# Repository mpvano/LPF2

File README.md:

## The LPF2 Filter Board

LPF2 is a combined Relay Switched Harmonic Filter, Receiver High Pass Filter, VSWR bridge and Antenna Relay board for Low Powered HF Radios. It is designed primarily for use with radio board sets that stack mechanically with the Raspberry Pi. and has been successfully used to build several different radios.

The LPF2 board is compatible for stacking with boards designed to the Raspberry Pi "Hat" specification, although it is not a "hat" as it is the same size as the Pi itself and overhangs the IO connectors. It can also be used as a standalone board with anything that can provide compatible I2C and TX/RX control signals, and 3.3 Volt and Relay Power.

It can be built to use 4.5 Volt relays powered from the GPIO connector or for 12 Volt relays powered from an external source.

## N2ADR Filter Compatibility

The board was designed for limited software compatibility with the popular N2ADR filter board used by the Hermes Lite 2 radio and widely supported in SDR software. The board is NOT completely compatible with N2ADR's design. It differs in the following ways:

  1. The receiver low pass filter is always active - the control bit is IGNORED
  2. There are only 5 Low Pass filters. The control bit for "160 meters" is IGNORED.
  3. The Most significant bit of the control word is wire or'ed with the external Transmit/Receive line allowing software T/R switching.
  4. The VSWR bridge uses a different ADC, so that it does not conflict with any HL2 compatible hardware in the radio - but this means it is not directly displayable by SDR software expecting the HL2 VSWR ADC.

The board has been used primarily with "Radioberry" and "RadioHat" Boards to build 5-10 watt 3-30Mhz Multimode Ham Transceivers.

## Filter Component Selection

The Low Pass Filters are not suitable for extremely dirty power amplifiers. They are designed to reduce the harmonic emissions from properly designed amplifiers within legal limits by reducing the harmonics - not totally eliminating them. As such, they may not work with single ended power amplifiers without modification to the filter values - The design expects the 2nd harmonic to be somewhat reduced by the power amplifier.

The filter component values are based on the popular ones originally published by the RSGB.

The VSWR bridge transformers are conservatively designed so that the diodes are protected in the event of higher power being applied. To improve the sensitivity, reduce the ratio to 10:1 or 7:1 and adjust the software used for power calculation accordingly.

Variations in filter material batches may requre trimming the Toroid coil values by 1 or two turns or spreading or compacting them.

## Hints

I suggest testing the board's logic functionality while assembling it before the relays and filter components are installed since rework is difficult once the relays are in place.

I've also provided the source for a simple TK python program I use to view the VSWR, power and battery voltage in a separate window on my radios.

## Disclaimers

I designed this board for my own use. I have no plans to provide PCBs or boards to others at this time. Hopefully, if there is interest in this board others will provide for group builds, completed boards, or group purchases.

Anyone may use this design for any purpose whatsoever, although I would prefer that it retain some credit to me as the original designer. I will not provide support for any boards using this design that have not been actually built by ME!

If you build any boards or devices using this design, you are totally responsible for any associated liabilities.

This design was only possible thanks to the excellent work done by George Dobbs G3RJV, James Ahlstrom N2ADR, and everyone associated with the HL2 and Radioberry projects.

Mario Vano
AE0GL

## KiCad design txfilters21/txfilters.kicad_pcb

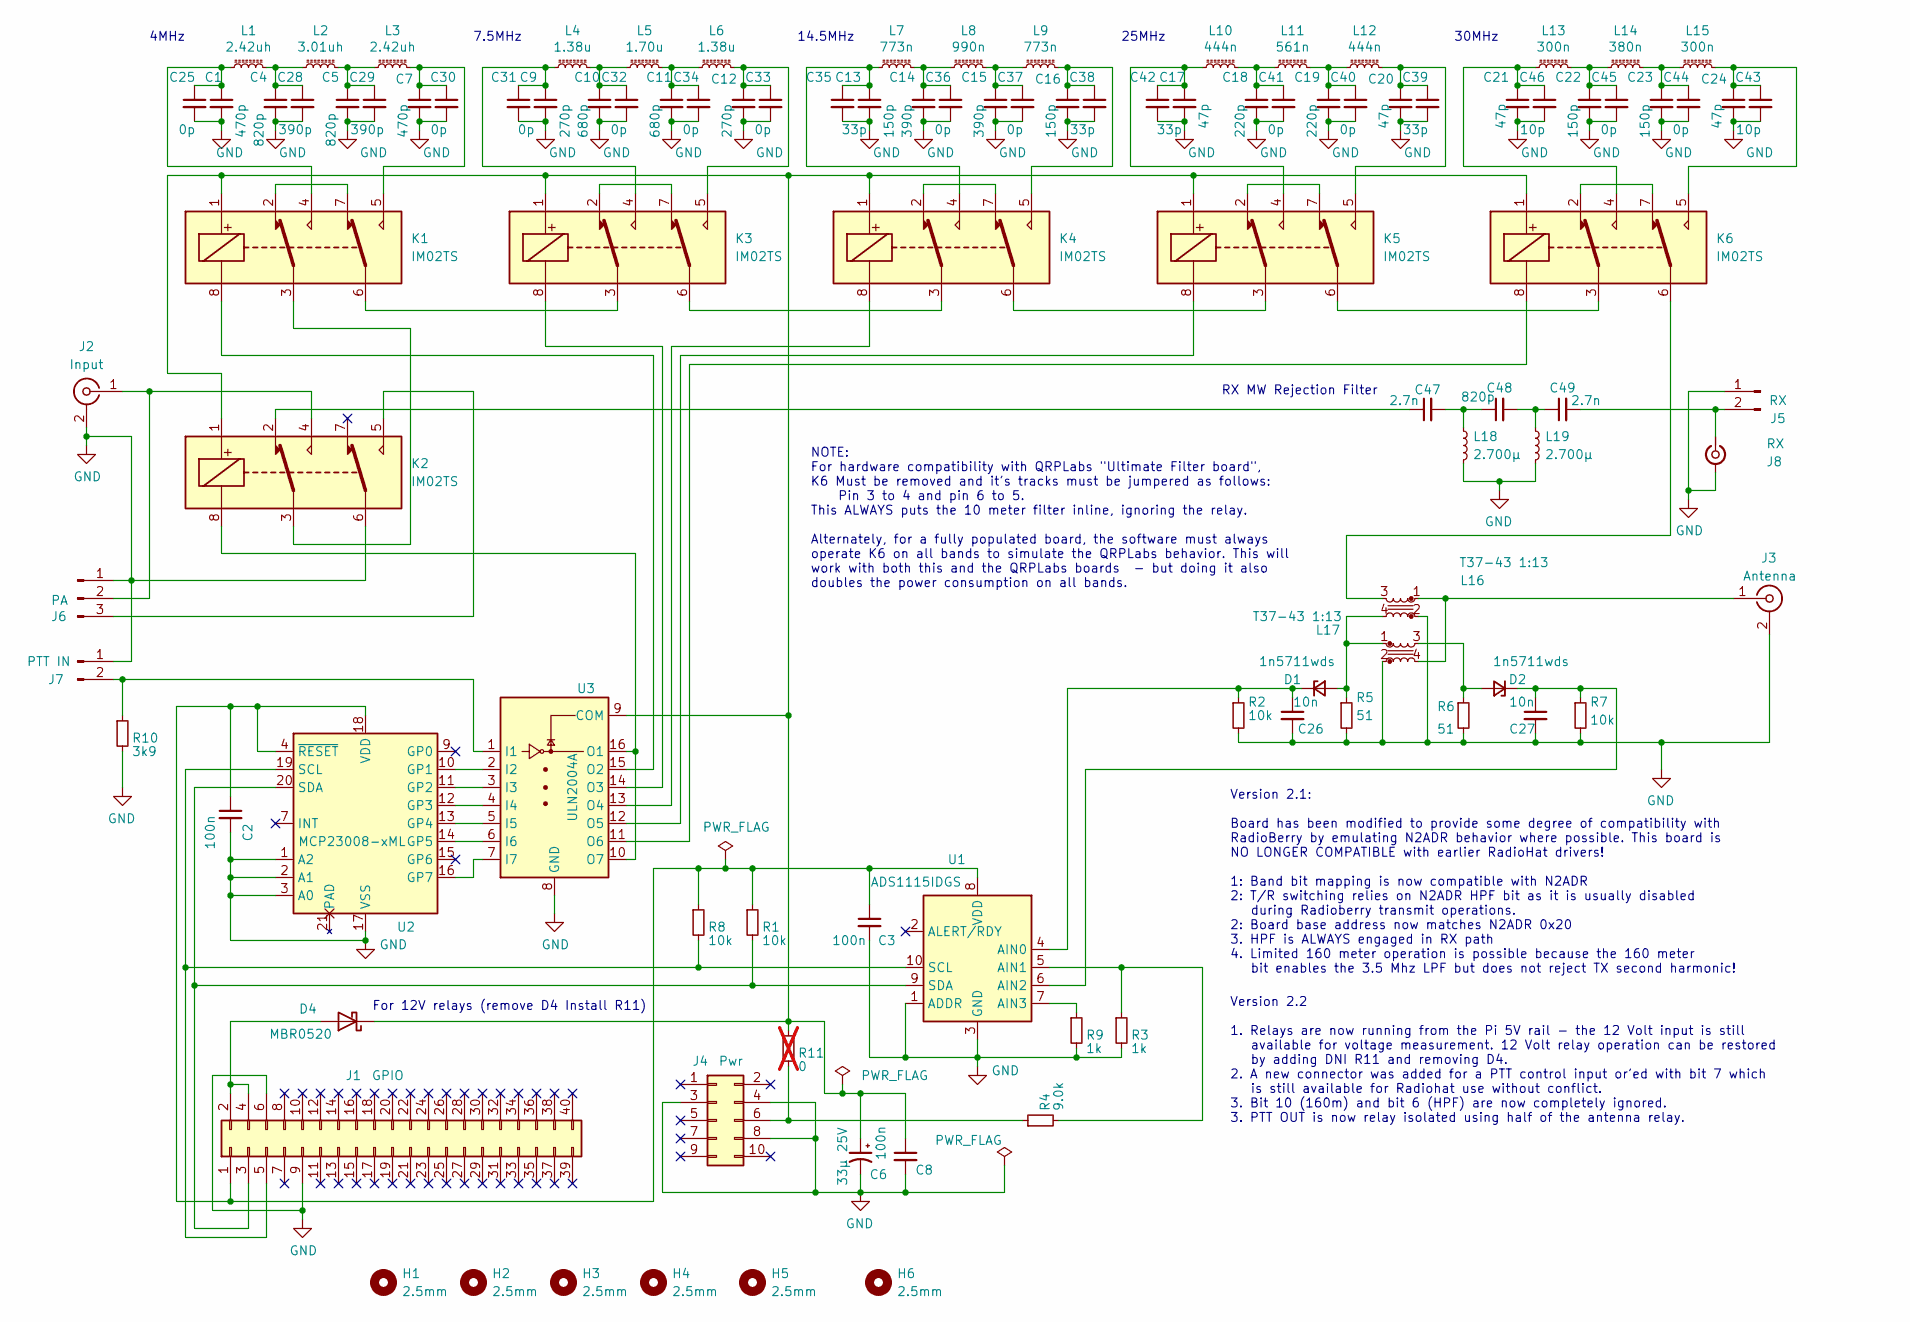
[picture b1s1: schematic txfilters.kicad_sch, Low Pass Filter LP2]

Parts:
C1, C7: 470p; C_1206_3216Metric; Manufacturer_Part_Number KGM31VCG2D471JU; DigiKey Part Number 478-KGM31VCG2D471JUCT-ND
C2, C3, C8: 100n; C_0603_1608Metric; Manufacturer_Part_Number CL10B104JB8NNNC; DigiKey Part Number 1276-1033-1-ND
C4, C5: 820p; C_1206_3216Metric; Manufacturer_Part_Number KGM31VCG2D821JU; DigiKey Part Number 478-KGM31VCG2D821JUCT-ND
C6: 33µ 25V; C_Elec_5x5.8; Manufacturer_Part_Number EEE-FK1E330UR; DigiKey Part Number PCE3802CT-ND
C9, C12: 270p; C_1206_3216Metric; Manufacturer_Part_Number KGM31BCG2D271JT; DigiKey Part Number 478-KGM31BCG2D271JTCT-ND
C10, C11: 680p; C_1206_3216Metric; Manufacturer_Part_Number KGM31VCG2D681JU; DigiKey Part Number 478-KGM31VCG2D681JUCT-ND
C13, C16, C22, C23: 150p; C_1206_3216Metric; Manufacturer_Part_Number KGM31BCG2D151JT; DigiKey Part Number 478-KGM31BCG2D151JTCT-ND
C14, C15, C28, C29: 390p; C_1206_3216Metric; Manufacturer_Part_Number KGM31BCG2D391JT; DigiKey Part Number 478-KGM31BCG2D391JTCT-ND
C17, C20, C21, C24: 47p; C_1206_3216Metric; Manufacturer_Part_Number KGM31BCG2D470JT; DigiKey Part Number 478-KGM31BCG2D470JTCT-ND
C18, C19: 220p; C_1206_3216Metric; Manufacturer_Part_Number KGM31BCG2D221JT; DigiKey Part Number 478-KGM31BCG2D221JTCT-ND
C25, C30, C31, C32, C33, C34, C36, C37, C40, C41, C44, C45: 0p; C_1206_3216Metric
C26, C27: 10n; C_0603_1608Metric; Manufacturer_Part_Number Samsung Electro-Mechanics; DigiKey Part Number 1276-1091-1-ND
C35, C38, C39, C42: 33p; C_1206_3216Metric; Manufacturer_Part_Number KGM31BCG2D330JT; DigiKey Part Number 478-KGM31BCG2D330JTCT-ND
C43, C46: 10p; C_1206_3216Metric; Manufacturer_Part_Number KGM31BCG2D100JT; DigiKey Part Number 478-KGM31BCG2D100JTCT-ND
C47, C49: 2.7n; C_0603_1608Metric
C48: 820p; C_0603_1608Metric
D1, D2: 1n5711wds; D_SOD-323_HandSoldering; Manufacturer_Part_Number 1N5711WS-7-F; DigiKey Part Number 1N5711WS-FDICT-ND
D4: MBR0520; D_SOD-123; DigiKey Part Number MBR0520LT1G
H1, H2, H3, H4, H5, H6: 2.5mm; MountingHole_2.7mm_M2.5_KA
J1: GPIO; PinSocket_2x20_P2.54mm_Vertical
J2: Input; SMA_Samtec_SMA-J-P-H-ST-EM1_EdgeMount
J3: Antenna; SMA_Samtec_SMA-J-P-H-ST-EM1_EdgeMount
J4: Pwr; PinSocket_2x05_P2.54mm_Vertical
J5: RX; JST_XH_B2B-XH-A_1x02_P2.50mm_Vertical
J6: PA; JST_XH_B3B-XH-A_1x03_P2.50mm_Vertical
J7: PTT IN; JST_PH_B2B-PH-K_1x02_P2.00mm_Vertical
J8: RX; U.FL_Molex_MCRF_73412-0110_Vertical
K1, K2, K3, K4, K5, K6: IM02TS; Relay_DPDT_AXICOM_IMSeries_Pitch5.08mm; Manufacturer_Part_Number 2-1462037; DigiKey Part Number PB1093-ND
L1, L3: 2.42uh; L_Toroid_Vertical_L14.0mm_W6.3mm_P4.57mm_Pulse_A
L2: 3.01uh; L_Toroid_Vertical_L14.0mm_W6.3mm_P4.57mm_Pulse_A
L4, L6: 1.38u; L_Toroid_Vertical_L14.0mm_W6.3mm_P4.57mm_Pulse_A
L5: 1.70u; L_Toroid_Vertical_L14.0mm_W6.3mm_P4.57mm_Pulse_A
L7, L9: 773n; L_Toroid_Vertical_L14.0mm_W6.3mm_P4.57mm_Pulse_A
L8: 990n; L_Toroid_Vertical_L14.0mm_W6.3mm_P4.57mm_Pulse_A
L10, L12: 444n; L_Toroid_Vertical_L14.0mm_W6.3mm_P4.57mm_Pulse_A
L11: 561n; L_Toroid_Vertical_L14.0mm_W6.3mm_P4.57mm_Pulse_A
L13, L15: 300n; L_Toroid_Vertical_L14.0mm_W6.3mm_P4.57mm_Pulse_A
L14: 380n; L_Toroid_Vertical_L14.0mm_W6.3mm_P4.57mm_Pulse_A
L16, L17: T37-43 1:13; Transformer_Toroid_Horizontal_D9.0mm_Amidon-T30
L18, L19: 2.700µ; L_0603_1608Metric
R1, R2, R7, R8: 10k; R_0603_1608Metric; Manufacturer_Part_Number RMCF0603FT10K0; DigiKey Part Number RMCF0603FT10K0CT-ND
R3, R9: 1k; R_0603_1608Metric; Manufacturer_Part_Number RMCF0603FT1K00; DigiKey Part Number RMCF0603FT1K00CT-ND
R4: 9.0k; R_0603_1608Metric; Manufacturer_Part_Number RMCF0603FT9K09; DigiKey Part Number RMCF0603FT9K09CT-ND
R5, R6: 51; R_0603_1608Metric; Manufacturer_Part_Number RMCF0603FT51R0; DigiKey Part Number RMCF0603FT51R0CT-ND
R10: 3k9; R_0603_1608Metric; Manufacturer_Part_Number RMCF0603FT10K0; DigiKey Part Number RMCF0603JT3K90
R11: 0; R_0603_1608Metric; Manufacturer_Part_Number RMCF0603FT10K0; DigiKey Part Number RMCF0603FT10K0CT-ND; not fitted
U1: ADS1115IDGS; TSSOP-10_3x3mm_P0.5mm; Manufacturer_Part_Number ADS1115IDGSR; DigiKey Part Number 296-38849-1-ND
U2: MCP23008-xML; QFN-20-1EP_4x4mm_P0.5mm_EP2.5x2.5mm; Manufacturer_Part_Number MCP23008T-E/ML; DigiKey Part Number MCP23008T-E/MLCT-ND
U3: ULN2004A; SOIC-16_3.9x9.9mm_P1.27mm; Manufacturer_Part_Number ULN2004ADR; DigiKey Part Number 4518-ULN2003ACT-ND

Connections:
GND: C1.2, C2.2, C3.2, C4.2, C5.2, C6.2, C7.2, C8.2, C9.2, C10.2, C11.2, C12.2, C13.2, C14.2, C15.2, C16.2, C17.2, C18.2, C19.2, C20.2, C21.2, C22.2, C23.2, C24.2, C25.2, C26.2, C27.2, C28.2, C29.2, C30.2, C31.2, C32.2, C33.2, C34.2, C35.2, C36.2, C37.2, C38.2, C39.2, C40.2, C41.2, C42.2, C43.2, C44.2, C45.2, C46.2, J1.6, J1.9, J2.2 (Ext), J3.2 (Ext), J4.3, J4.4, J4.8, J5.1, J6.1, J7.1, J8.2 (Ext), K2.6, L16.2, L17.2, L18.2, L19.2, R2.2, R3.2, R5.2, R6.2, R7.2, R9.2, R10.2, U1.1 (ADDR), U1.3 (GND), U2.1 (A2), U2.2 (A1), U2.3 (A0), U2.17 (VSS), U3.8 (GND)
unnamed: C1.1, C25.1, K1.4, L1.2
unnamed: C10.1, C32.1, L4.1, L5.2
unnamed: C11.1, C34.1, L5.1, L6.2
unnamed: C12.1, C33.1, K3.5, L6.1
unnamed: C13.1, C35.1, K4.4, L7.2
unnamed: C14.1, C36.1, L7.1, L8.2
unnamed: C15.1, C37.1, L8.1, L9.2
unnamed: C16.1, C38.1, K4.5, L9.1
unnamed: C17.1, C42.1, K5.4, L10.2
unnamed: C18.1, C41.1, L10.1, L11.2
unnamed: C19.1, C40.1, L11.1, L12.2
unnamed: C20.1, C39.1, K5.5, L12.1
unnamed: C21.1, C46.1, K6.4, L13.2
unnamed: C22.1, C45.1, L13.1, L14.2
unnamed: C23.1, C44.1, L14.1, L15.2
unnamed: C24.1, C43.1, K6.5, L15.1
unnamed: C4.1, C28.1, L1.1, L2.2
unnamed: C5.1, C29.1, L2.1, L3.2
unnamed: C7.1, C30.1, K1.5, L3.1
unnamed: C9.1, C31.1, K3.4, L4.2
unnamed: C47.1, K2.2
unnamed: C47.2, C48.1, L18.1
unnamed: C48.2, C49.1, L19.1
unnamed: D1.2 (A), L16.4, L17.1, R5.1
unnamed: C26.1, D1.1 (K), R2.1, U1.4 (AIN0)
unnamed: D2.2 (A), L17.3, R6.1
unnamed: C27.1, D2.1 (K), R7.1, U1.6 (AIN2)
unnamed: D4.2 (A), J1.2, J1.4
unnamed: C6.1, C8.1, D4.1 (K), K1.1, K2.1, K3.1, K4.1, K5.1, K6.1, R11.1, U3.9 (COM)
unnamed: C2.1, C3.1, J1.1, R1.1, R8.1, U1.8 (VDD), U2.4 (~RESET), U2.18 (VDD)
unnamed: J1.3, R1.2, U1.9 (SDA), U2.20 (SDA)
unnamed: J1.5, R8.2, U1.10 (SCL), U2.19 (SCL)
unnamed: J2.1 (In), J6.2, K2.4
unnamed: J3.1 (In), L16.1, L17.4
unnamed: J4.6, R4.1, R11.2
unnamed: C49.2, J5.2, J8.1 (In)
unnamed: J6.3, K2.5
unnamed: J7.2, R10.1, U3.1 (I1)
unnamed: K1.2, K1.7
unnamed: K1.3, K2.3
unnamed: K1.6, K3.3
unnamed: K3.2, K3.7
unnamed: K3.6, K4.3
unnamed: K4.2, K4.7
unnamed: K4.6, K5.3
unnamed: K5.2, K5.7
unnamed: K5.6, K6.3
unnamed: K6.2, K6.7
unnamed: K6.6, L16.3
unnamed: R3.1, R4.2, U1.5 (AIN1)
unnamed: R9.1, U1.7 (AIN3)
unnamed: U2.10 (GP1), U3.2 (I2)
unnamed: U2.11 (GP2), U3.3 (I3)
unnamed: U2.12 (GP3), U3.4 (I4)
unnamed: U2.13 (GP4), U3.5 (I5)
unnamed: U2.14 (GP5), U3.6 (I6)
unnamed: U2.16 (GP7), U3.7 (I7)
unnamed: K2.8, U3.10 (O7), U3.16 (O1)
unnamed: K1.8, U3.15 (O2)
unnamed: K3.8, U3.14 (O3)
unnamed: K4.8, U3.13 (O4)
unnamed: K5.8, U3.12 (O5)
unnamed: K6.8, U3.11 (O6)

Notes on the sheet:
30MHz
7.5MHz
Version 2.1: Board has been modified to provide some degree of compatibility with RadioBerry by emulating N2ADR behavior where possible. This board is NO LONGER COMPATIBLE with earlier RadioHat drivers! 1: Band bit mapping is now compatible with N2ADR 2: T/R switching relies on N2ADR HPF bit as it 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
25MHz
RX MW Rejection Filter
4MHz
14.5MHz
Version 2.2 1. Relays are now running from the Pi 5V rail - the 12 Volt input is still available for voltage measurement. 12 Volt relay operation can be restored by adding DNI R11 and removing D4. 2. A new connector was added for a PTT control input or'ed with bit 7 which is still available for Rad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
NOTE: For hardware compatibility with QRPLabs "Ultimate Filter board", K6 Must be removed and it's tracks must be jumpered as follows: Pin 3 to 4 and pin 6 to 5. This ALWAYS puts the 10 meter filter inline, ignoring the relay. Alternately, for a fully populated board, the software must always opera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
For 12V relays (remove D4 Install R11)

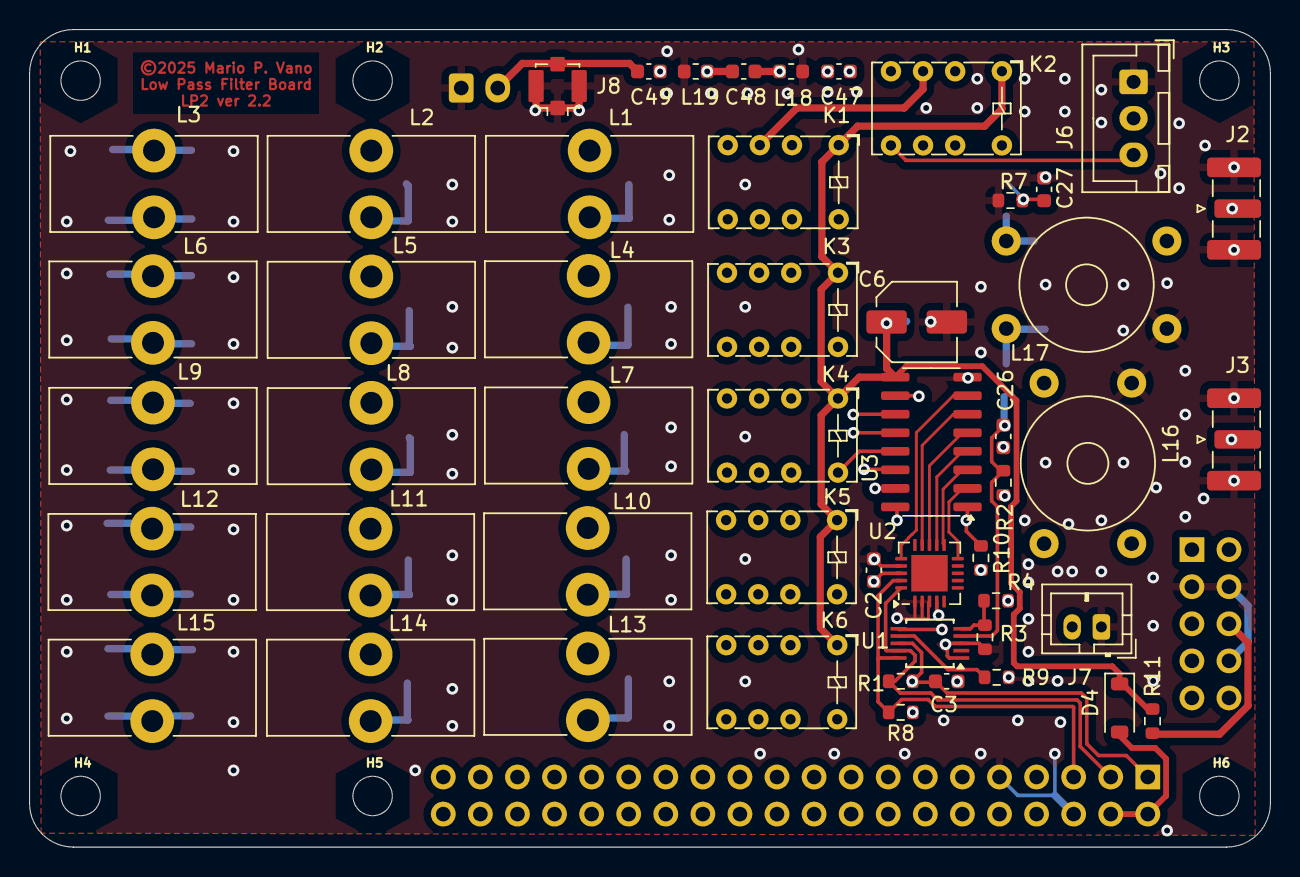
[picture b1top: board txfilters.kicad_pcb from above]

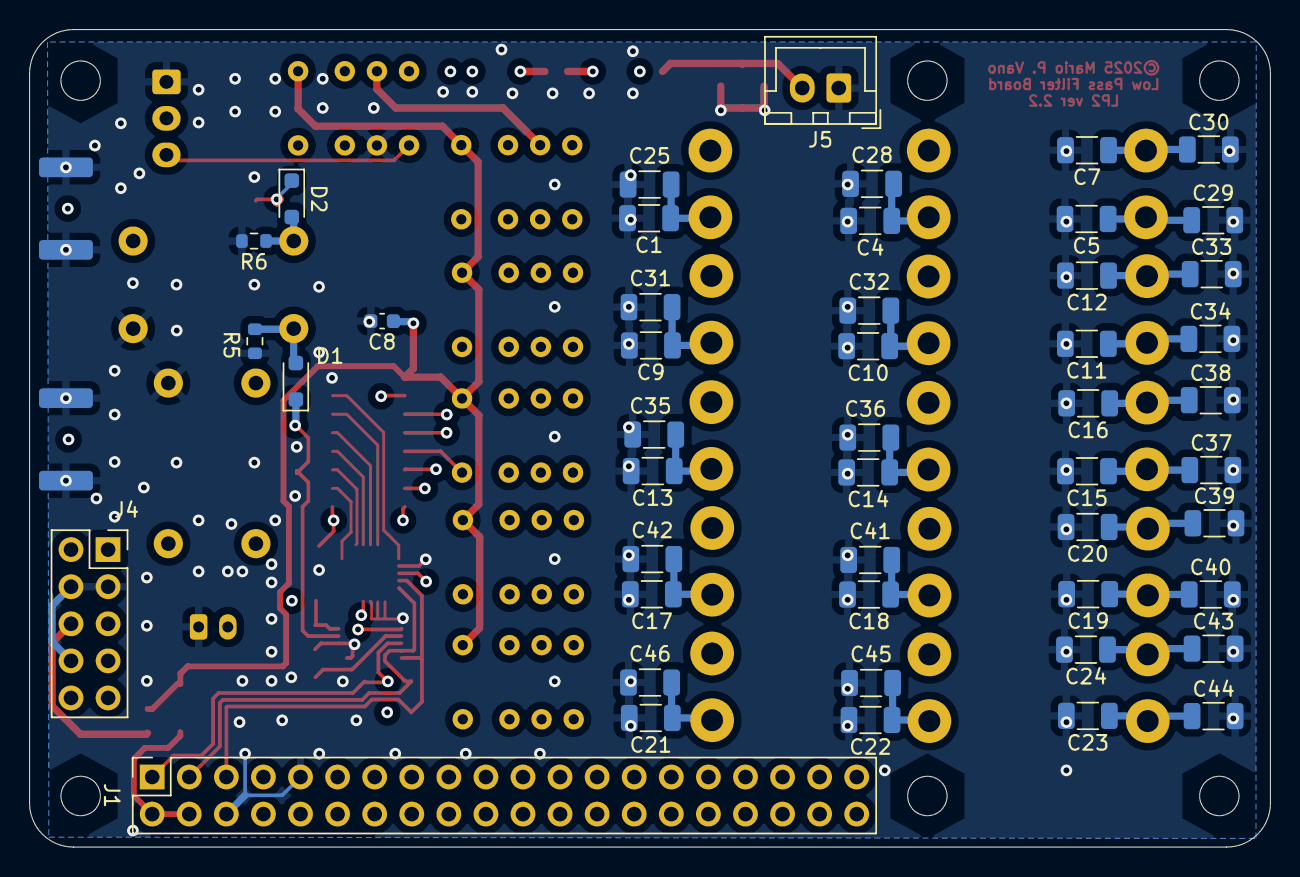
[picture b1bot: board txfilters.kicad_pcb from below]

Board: 4 copper layers, 85.0 x 56.0 mm, 105 parts (48 on the bottom side), 64 nets.

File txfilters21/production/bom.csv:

Designator,Footprint,Quantity,Value,LCSC Part #
"C1, C7",1206,2,470p,
"C10, C11",1206,2,680p,
"C12, C9",1206,2,270p,
"C13, C16, C22, C23",1206,4,150p,
"C14, C15, C28, C29",1206,4,390p,
"C17, C20, C21, C24",1206,4,47p,
"C18, C19",1206,2,220p,
"C2, C3, C8",0603,3,100n,
"C25, C30, C31, C32, C33, C34, C36, C37, C40, C41, C44, C45",1206,12,0p,
"C26, C27",0603,2,10n,
"C35, C38, C39, C42",1206,4,33p,
"C4, C5",1206,2,820p,
"C43, C46",1206,2,10p,
"C47, C49",0603,2,2.7n,
C48,0603,1,820p,
C6,C_Elec_5x5.8,1,33µ 25V,
"D1, D2",D_SOD-323_HandSoldering,2,1n5711wds,
D4,D_SOD-123,1,MBR0520,
"H1, H2, H3, H4, H5, H6",MountingHole_2.7mm_M2.5_KA,6,2.5mm,
J1,PinSocket_2x20_P2.54mm_Vertical,1,GPIO,
J2,SMA_Samtec_SMA-J-P-H-ST-EM1_EdgeMount,1,Input,
J3,SMA_Samtec_SMA-J-P-H-ST-EM1_EdgeMount,1,Antenna,
J4,PinSocket_2x05_P2.54mm_Vertical,1,Pwr,
J5,JST_XH_B2B-XH-A_1x02_P2.50mm_Vertical,1,RX,
J6,JST_XH_B3B-XH-A_1x03_P2.50mm_Vertical,1,PA,
J7,JST_PH_B2B-PH-K_1x02_P2.00mm_Vertical,1,PTT IN,
J8,U.FL_Molex_MCRF_73412-0110_Vertical,1,RX,
"K1, K2, K3, K4, K5, K6",Relay_DPDT_AXICOM_IMSeries_Pitch5.08mm,6,IM02TS,
"L1, L3",L_Toroid_Vertical_L14.0mm_W6.3mm_P4.57mm_Pulse_A,2,2.42uh,
"L10, L12",L_Toroid_Vertical_L14.0mm_W6.3mm_P4.57mm_Pulse_A,2,444n,
L11,L_Toroid_Vertical_L14.0mm_W6.3mm_P4.57mm_Pulse_A,1,561n,
"L13, L15",L_Toroid_Vertical_L14.0mm_W6.3mm_P4.57mm_Pulse_A,2,300n,
L14,L_Toroid_Vertical_L14.0mm_W6.3mm_P4.57mm_Pulse_A,1,380n,
"L16, L17",Transformer_Toroid_Horizontal_D9.0mm_Amidon-T30,2,T37-43 1:13,
"L18, L19",0603,2,2.700µ,
L2,L_Toroid_Vertical_L14.0mm_W6.3mm_P4.57mm_Pulse_A,1,3.01uh,
"L4, L6",L_Toroid_Vertical_L14.0mm_W6.3mm_P4.57mm_Pulse_A,2,1.38u,
L5,L_Toroid_Vertical_L14.0mm_W6.3mm_P4.57mm_Pulse_A,1,1.70u,
"L7, L9",L_Toroid_Vertical_L14.0mm_W6.3mm_P4.57mm_Pulse_A,2,773n,
L8,L_Toroid_Vertical_L14.0mm_W6.3mm_P4.57mm_Pulse_A,1,990n,
"R1, R2, R7, R8",0603,4,10k,
R10,0603,1,3k9,
"R3, R9",0603,2,1k,
R4,0603,1,9.0k,
"R5, R6",0603,2,51,
U1,TSSOP-10_3x3mm_P0.5mm,1,ADS1115IDGS,
U2,QFN-20-1EP_4x4mm_P0.5mm_EP2.5x2.5mm,1,MCP23008-xML,
U3,SOIC-16_3.9x9.9mm_P1.27mm,1,ULN2003A,

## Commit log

2025-09-02 Initial Upload
2025-09-02 added gitignore
2025-09-02 kicad ignores
2025-09-02 Added sample VSWR display
    Added a simple TK python program for viewing the VSWR, power and battery voltage in a "kilroy" window peeking over the top of your SDR program..
2025-09-02 Update README typos and add vswr viewer note

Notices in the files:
txfilters21/txfilters.kicad_pcb:
©2025 Mario P. Vano
txfilters21/txfilters.kicad_sch:
©2024 Mario P. Vano Low Pass Filter Board LP2 ver 2.2
